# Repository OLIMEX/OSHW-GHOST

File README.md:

# OSHW-GHOST
Small SMT soldering kit with PIC10F206 re-programmable microcontroller, capacitive sensor and LEDs

## License
* Hardware is released under CERN Open Hardware Licence Version 2 - Strongly Reciprocal https://spdx.org/licenses/CERN-OHL-S-2.0.html
* Software is released under GPL3 License
* Documentation is released under CC BY-SA 4.0 https://creativecommons.org/licenses/by-sa/4.0/

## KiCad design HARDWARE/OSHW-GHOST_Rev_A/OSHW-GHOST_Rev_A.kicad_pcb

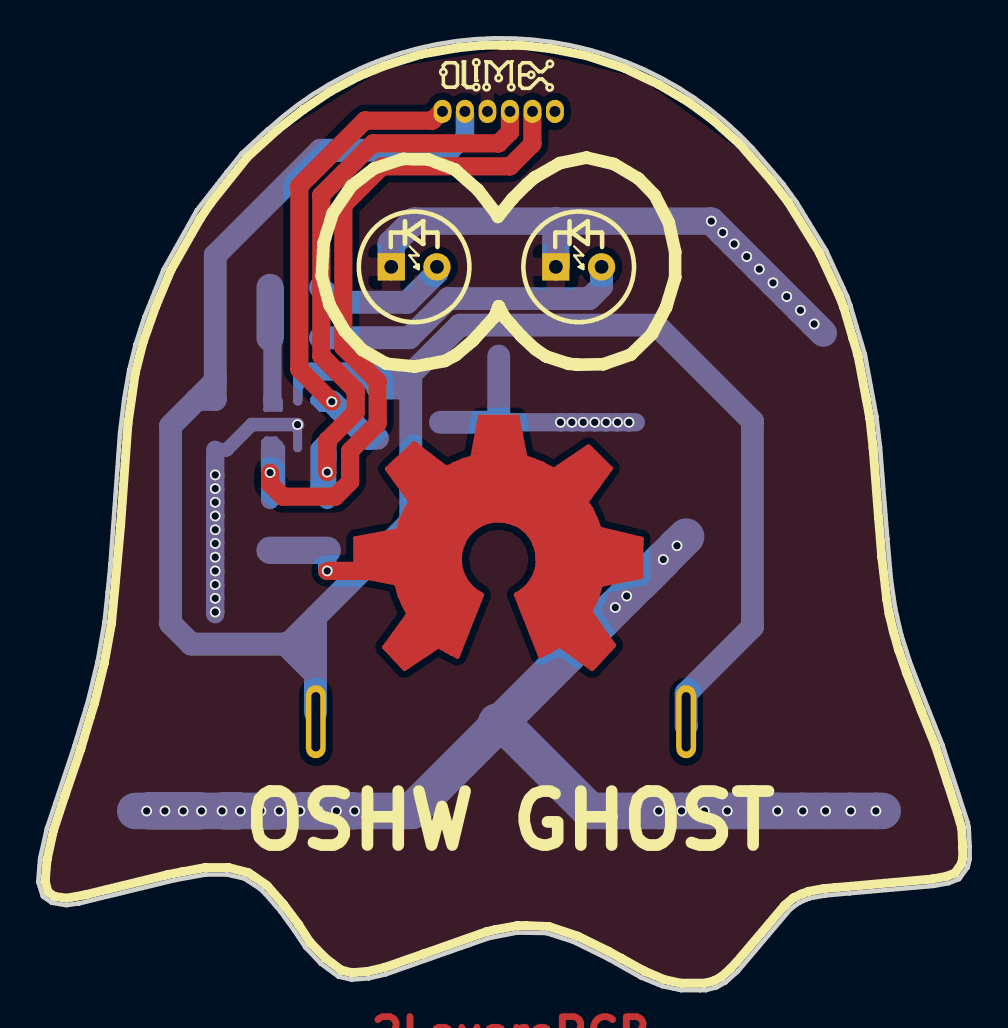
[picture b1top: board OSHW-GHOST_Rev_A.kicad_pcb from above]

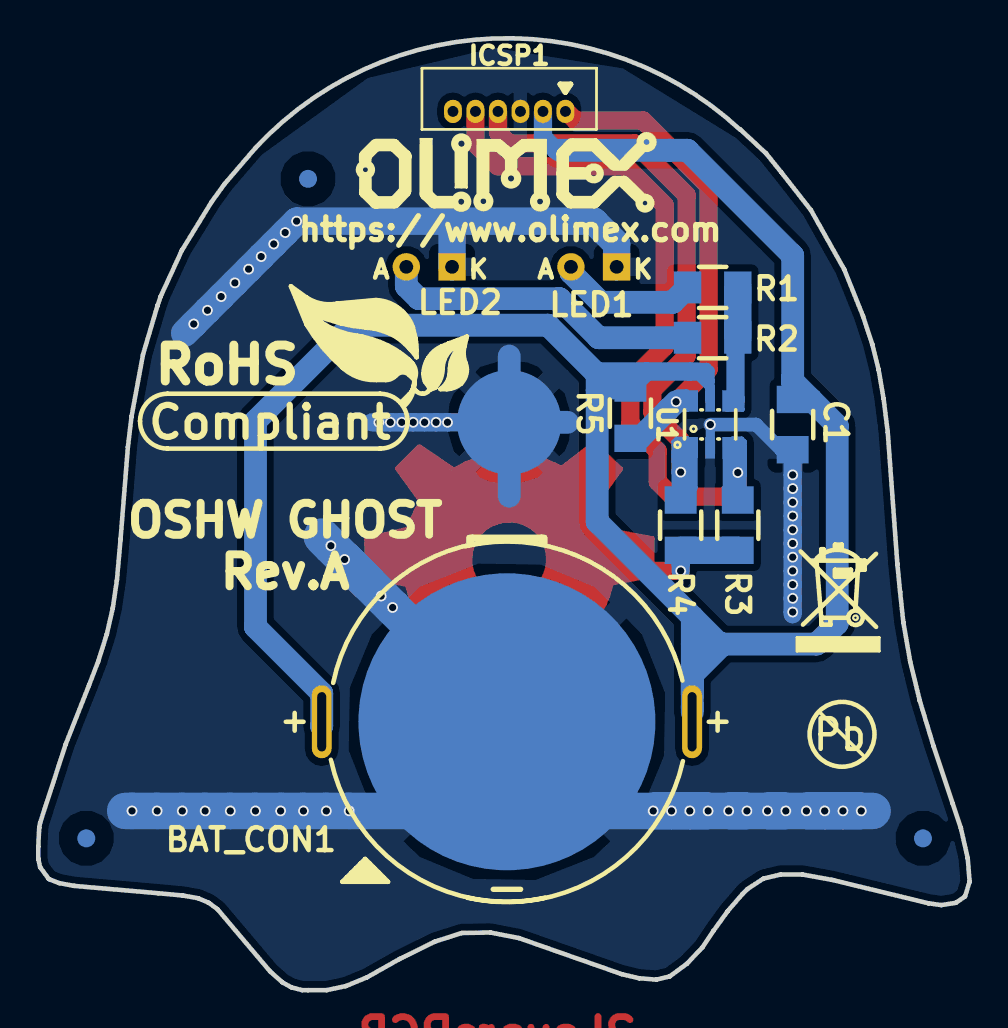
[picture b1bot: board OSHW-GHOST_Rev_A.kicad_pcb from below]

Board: 2 copper layers, 51.7 x 52.9 mm, 14 parts (11 on the bottom side), 9 nets.

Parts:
BAT_CON1: CR2032H_PTH
BPC1: BADGE-PIN-CLIPS
C1: 100nF/50V/20%/Y5V/C1206; C_1206_5MIL_DWS
CB1: CAP_BUT; CAP_BUT_LOGO_OPENHARDWARE_16x16
ICSP1: NA(WU06S); ICSP-WU06S
LED1, LED2: LED-3.0MM/GREEN; LED-3mm-PTH-KA
R1, R2, R4: 120R/R1206; R_1206_5MIL_DWS
R3: 1M/R1206; R_1206_5MIL_DWS
R5: NA(10k/R1206); R_1206_5MIL_DWS
Ref**: Val**; LOGO_ROHS_1
U1: PIC10F206T-I/OT(SOT23-6); SOT23-6

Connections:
+3V3: BAT_CON1.1, C1.1, ICSP1.2, R5.1, U1.5
/CLK: ICSP1.5, R3.1, U1.3
/DAT: ICSP1.4, R4.1, U1.1
/LED: R1.1, R2.1, U1.4
/MCLR: ICSP1.1, R5.2, U1.6
GND: BAT_CON1.2, BPC1.1, C1.2, ICSP1.3, LED1.1, LED2.1, U1.2
unnamed: CB1.1, R3.2, R4.2
unnamed: LED1.2, R1.2
unnamed: LED2.2, R2.2

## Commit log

2016-11-08 Initial file upload
2018-09-18 Update
    PDF BOM
